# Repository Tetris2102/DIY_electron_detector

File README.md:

# DIY_electron_detector

A modification of beta radiation (electron) detector by CERN's S'Cool Lab. Features compact design, adjuatable onboard amplification and increased sensitivity (12 diodes instead of 4). Uses BPW34F diodes. Currently not tested.

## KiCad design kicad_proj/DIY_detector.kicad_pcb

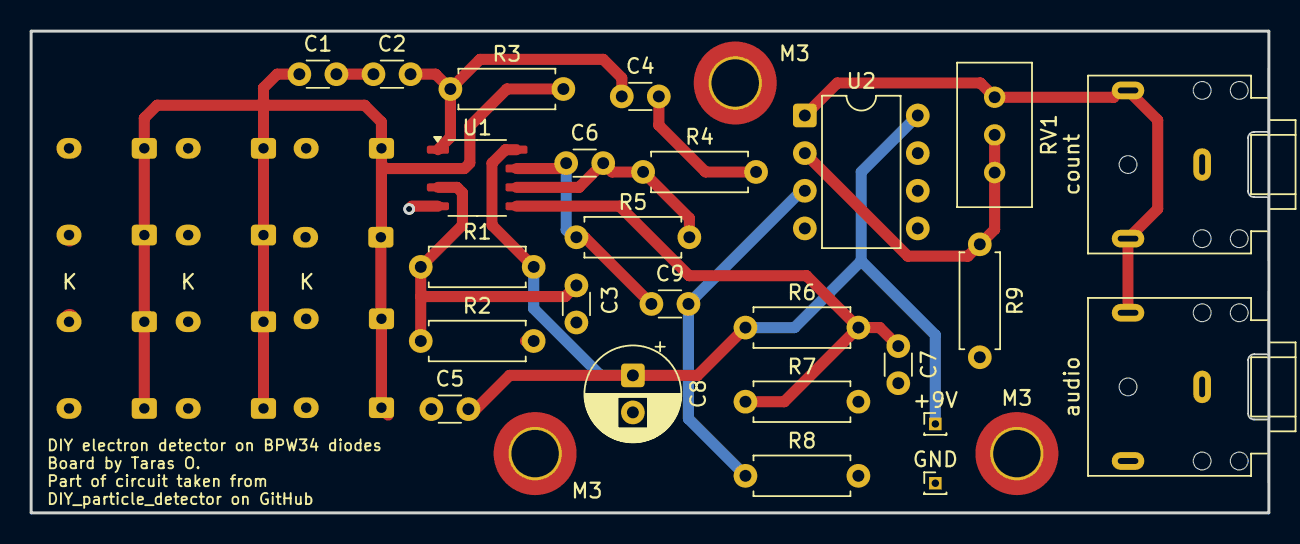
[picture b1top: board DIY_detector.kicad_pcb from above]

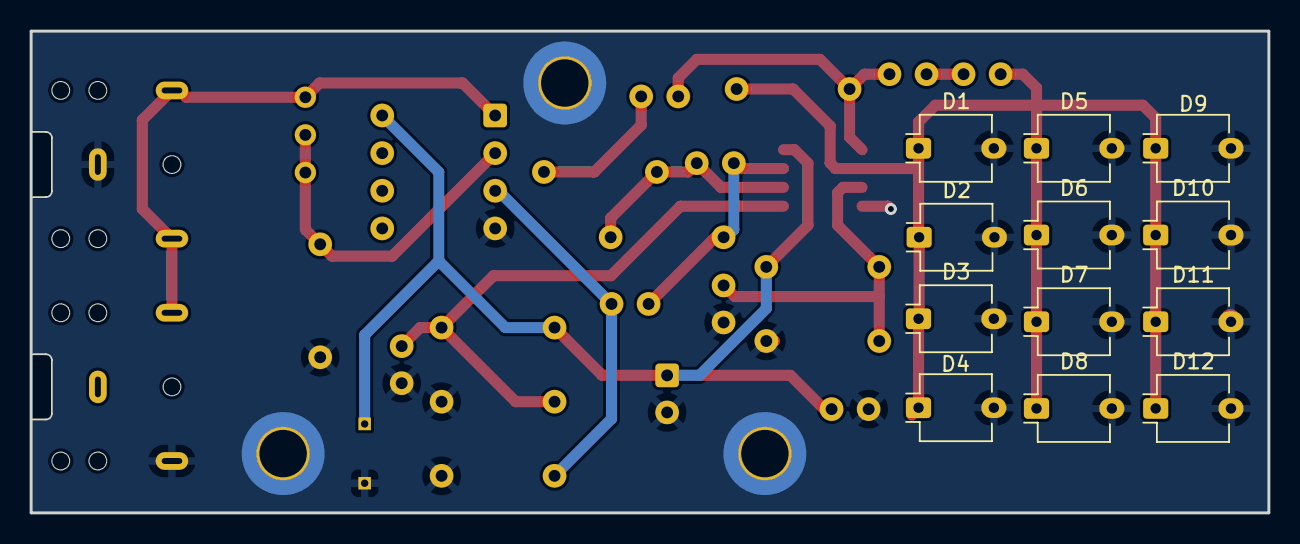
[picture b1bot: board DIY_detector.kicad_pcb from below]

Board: 2 copper layers, 83.5 x 32.5 mm, 40 parts (12 on the bottom side), 13 nets.

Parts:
+9V: +9V; PinHeader_1x01_P1.00mm_Vertical
C1, C2, C6: 10p; C_Disc_D3.0mm_W1.6mm_P2.50mm
C3, C4, C5, C7, C9: 100n; C_Disc_D3.0mm_W1.6mm_P2.50mm
C8: 47u; CP_Radial_D6.3mm_P2.50mm
D1, D8, D12: BPX61; Osram_DIL2_4.3x4.65mm_P5.08mm
D2, D3, D4, D5, D6, D7, D9, D10, D11: DNP; Osram_DIL2_4.3x4.65mm_P5.08mm
GND: GND; PinHeader_1x01_P1.00mm_Vertical
M3, M3#2, M3#3: M3 support; MountingHole_3.2mm_M3_DIN965_Pad_TopBottom
R1: 4k7; R_Axial_DIN0207_L6.3mm_D2.5mm_P7.62mm_Horizontal
R2: 15k; R_Axial_DIN0207_L6.3mm_D2.5mm_P7.62mm_Horizontal
R3: 10M; R_Axial_DIN0207_L6.3mm_D2.5mm_P7.62mm_Horizontal
R4: 1K; R_Axial_DIN0207_L6.3mm_D2.5mm_P7.62mm_Horizontal
R5: 100k; R_Axial_DIN0207_L6.3mm_D2.5mm_P7.62mm_Horizontal
R6, R7: 10k; R_Axial_DIN0207_L6.3mm_D2.5mm_P7.62mm_Horizontal
R8: 2k2; R_Axial_DIN0207_L6.3mm_D2.5mm_P7.62mm_Horizontal
R9: 3k3; R_Axial_DIN0207_L6.3mm_D2.5mm_P7.62mm_Horizontal
RV1: 100k; Potentiometer_Bourns_3296W_Vertical
U1: OPA2140; JEITA_SOIC-8_3.9x4.9mm_P1.27mm
U2: LM358; DIP-8_W7.62mm
audio: audio; Jack_3.5mm_CUI_SJ1-3523N_Horizontal
count: spectrum; Jack_3.5mm_CUI_SJ1-3523N_Horizontal

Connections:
+9V: +9V.1, C5.2, C8.1, R1.2, R6.1, U1.8 (Vcc), U2.8 (V+)
/Output: C9.2, R8.1, U2.3 (+)
GND: C3.2, C5.1, C7.2, C8.2, D1.2 (A), D2.2 (A), D3.2 (A), D4.2 (A), D5.2 (A), D6.2 (A), D7.2 (A), D8.2 (A), D9.2 (A), D10.2 (A), D11.2 (A), D12.2 (A), GND.1, M3.1, M3#2.1, M3#3.1, R2.2, R7.2, R8.2, R9.2, U1.4 (Gnd), U2.4 (V-), audio.R, count.S
unnamed: C1.2, C2.1
unnamed: C4.2, R4.2
unnamed: C1.1, D1.1 (K), D2.1 (K), D3.1 (K), D4.1 (K), D5.1 (K), D6.1 (K), D7.1 (K), D8.1 (K), D9.1 (K), D10.1 (K), D11.1 (K), D12.1 (K), R3.2, U1.2 (In1-)
unnamed: RV1.3, U2.1, audio.T, count.R, count.T
unnamed: C3.1, R1.1, R2.1, U1.3 (In1+)
unnamed: C7.1, R6.2, R7.1, U1.5 (In2+)
unnamed: C6.2, R4.1, R5.2, U1.6 (In2-)
unnamed: C2.2, C4.1, R3.1, U1.1 (Out1)
unnamed: C6.1, C9.1, R5.1, U1.7 (Out2)
unnamed: R9.1, RV1.1, RV1.2, U2.2 (-)

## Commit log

2025-08-24 Update LICENSE
2025-08-24 Fixed file locations

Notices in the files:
kicad_proj/DIY_detector.kicad_pcb:
CERN open hardware license V1.2
